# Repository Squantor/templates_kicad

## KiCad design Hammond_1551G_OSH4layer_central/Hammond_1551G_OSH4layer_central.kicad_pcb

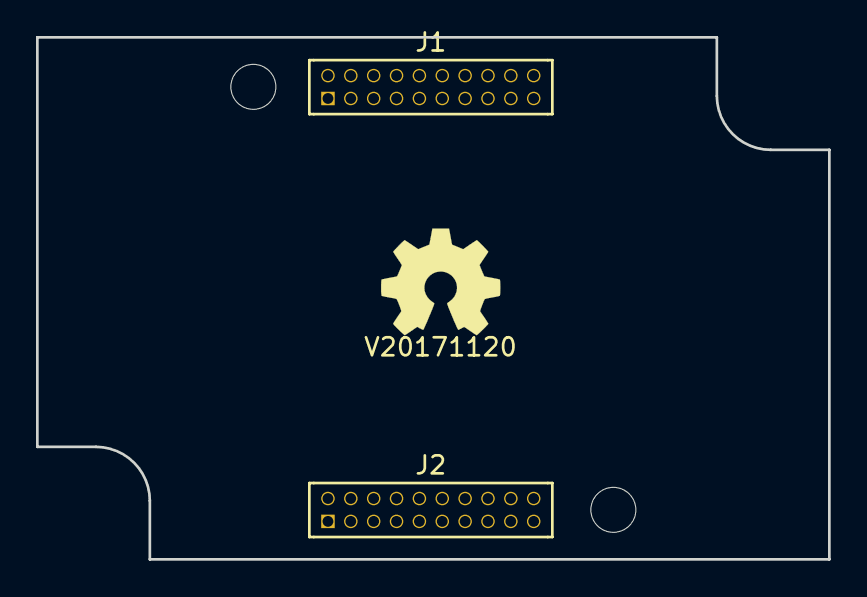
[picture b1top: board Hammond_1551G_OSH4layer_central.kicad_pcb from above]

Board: 4 copper layers, 44.0 x 29.0 mm, 6 parts (0 on the bottom side), 4 nets, no tracks yet.

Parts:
H1, H2: Drill_Hole_no_metal; MountingHole_2.5mm_no_metal
J1, J2: Conn_02x10_Odd_Even; Header-0127-2X10-H006
N1: OHWLOGO; OSHW-Symbol_6.7x6mm_SilkScreen
N2: V20171120; Label_version

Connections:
VDD: J2.1, J2.2
VDDA: J1.1, J1.2
VSS: J2.3, J2.4
VSSA: J1.3, J1.4
